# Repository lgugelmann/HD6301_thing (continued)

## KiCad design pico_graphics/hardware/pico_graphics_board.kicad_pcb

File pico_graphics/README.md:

# Pico Graphics

## TODOs for next revision

- reset button for the pico
- figure out the powerup problems
- R/W interface + interrupts

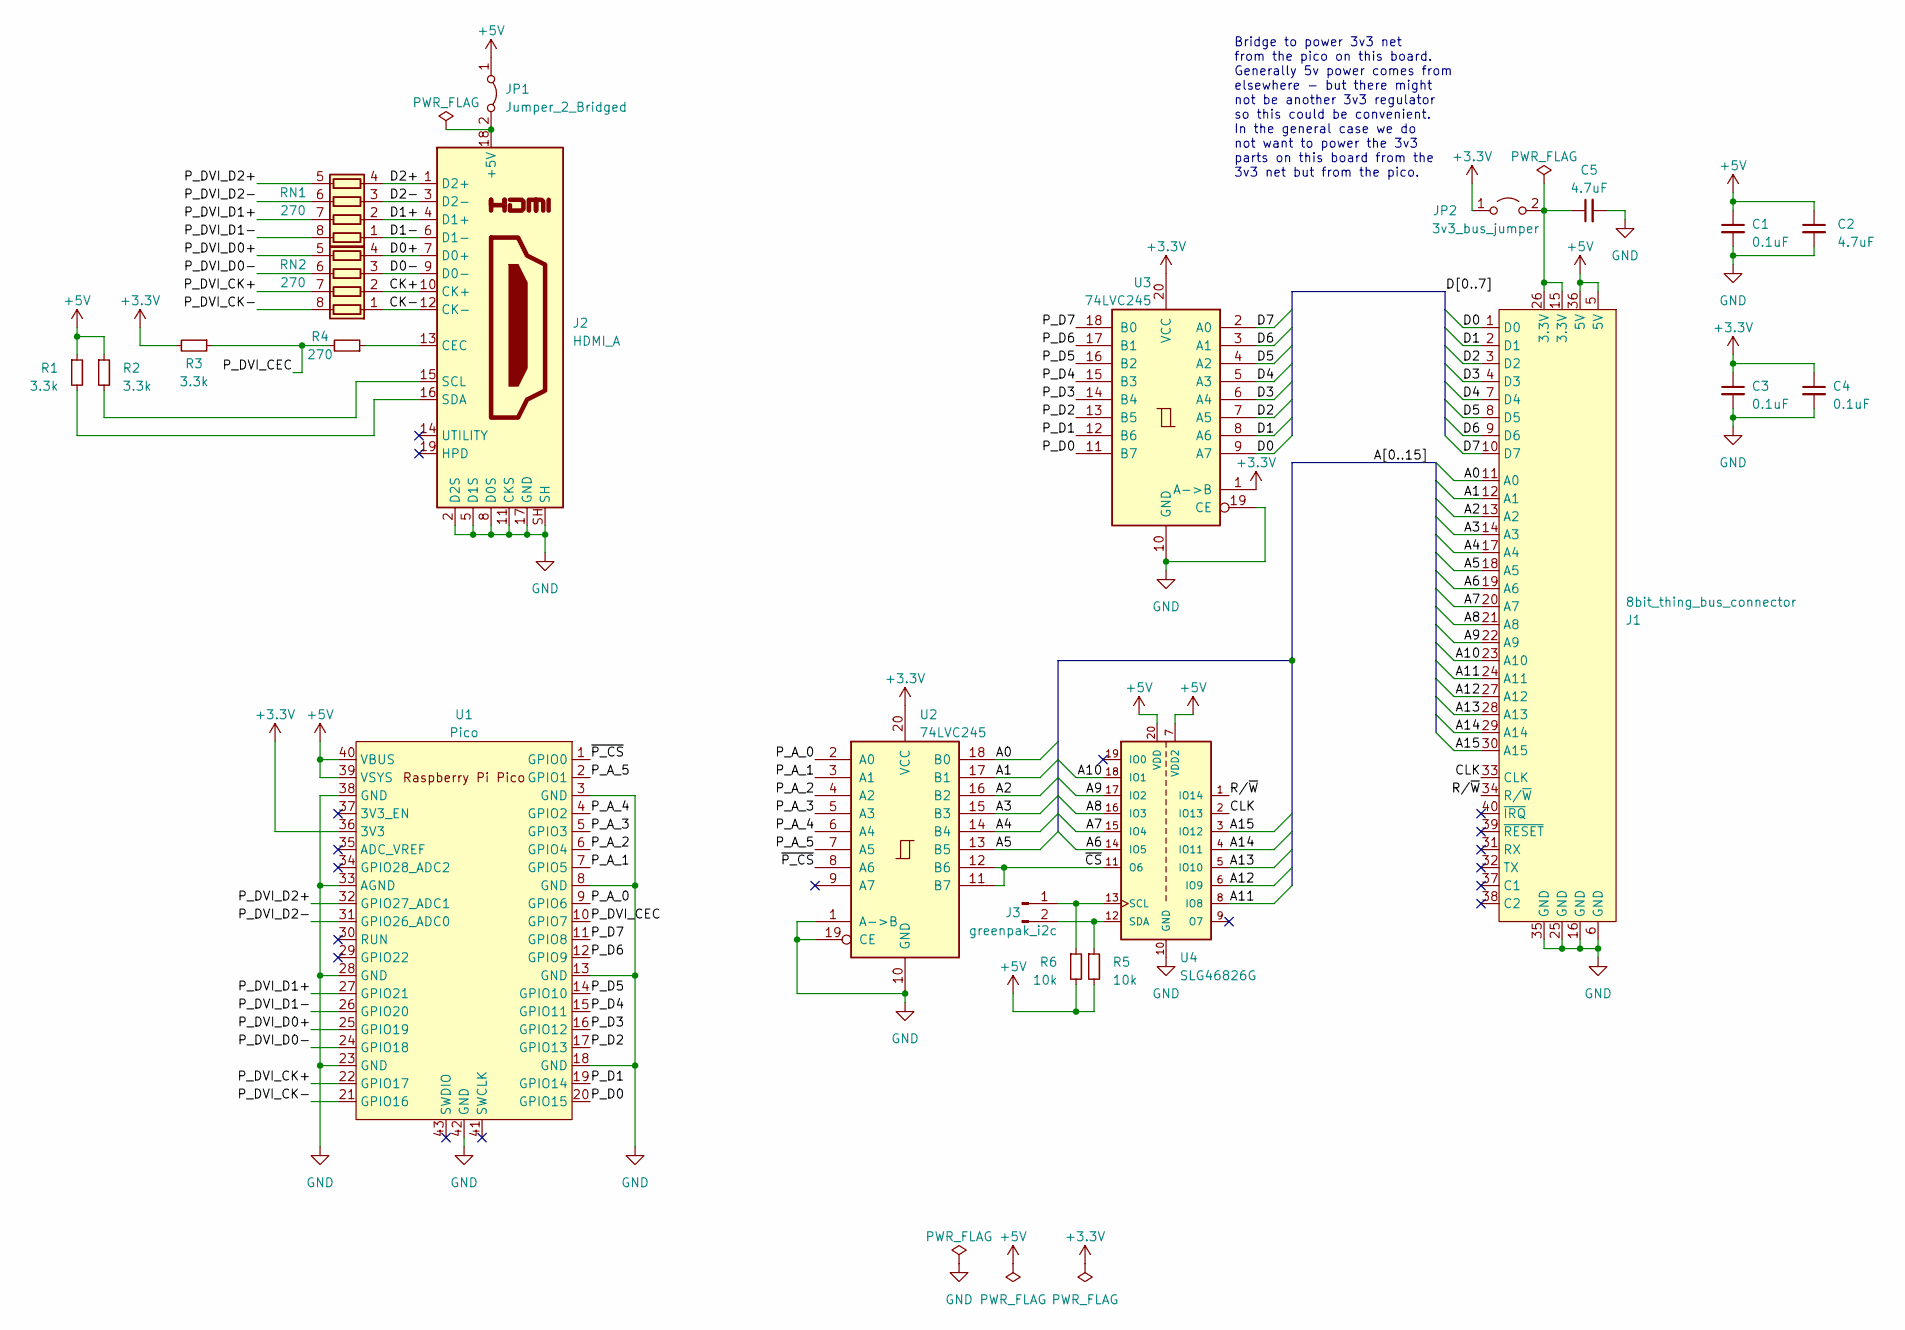
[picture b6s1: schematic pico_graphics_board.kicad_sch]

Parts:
C1, C3, C4: 0.1uF; C_0805_2012Metric_Pad1.18x1.45mm_HandSolder
C2, C5: 4.7uF; C_0805_2012Metric_Pad1.18x1.45mm_HandSolder
J1: 8bit_thing_bus_connector; IDC-Header_2x20_P2.54mm_Horizontal
J2: HDMI_A; HDMI_A_Amphenol_10029449-x01xLF_Horizontal
J3: greenpak_i2c; PinHeader_1x02_P2.54mm_Vertical_minimal
JP1: Jumper_2_Bridged; R_0805_2012Metric_Pad1.20x1.40mm_HandSolder
JP2: 3v3_bus_jumper; PinHeader_1x02_P2.54mm_Vertical_minimal
R1, R2, R3: 3.3k; R_0805_2012Metric_Pad1.20x1.40mm_HandSolder
R4: 270; R_0805_2012Metric_Pad1.20x1.40mm_HandSolder
R5, R6: 10k; R_0805_2012Metric_Pad1.20x1.40mm_HandSolder
RN1, RN2: 270; R_Array_Concave_4x0603
U1: Pico; RPi_Pico_SMD_TH
U2, U3: 74LVC245; TSSOP-20_4.4x6.5mm_P0.65mm
U4: SLG46826G; TSSOP-20_4.4x6.5mm_P0.65mm; PARTREV 3.10

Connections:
+3.3V: C3.1, C4.1, JP2.1 (A), R3.2, U1.36 (3V3), U2.20 (VCC), U3.1 (A->B), U3.20 (VCC)
+5V: C1.1, C2.1, J1.5 (5V), J1.36 (5V), JP1.1 (A), R1.1, R2.1, R5.2, R6.2, U1.39 (VSYS), U1.40 (VBUS), U4.7 (VDD2), U4.20 (VDD)
/A0: J1.11 (A0), U2.18 (B0)
/A1: J1.12 (A1), U2.17 (B1)
/A2: J1.13 (A2), U2.16 (B2)
/A3: J1.14 (A3), U2.15 (B3)
/A4: J1.17 (A4), U2.14 (B4)
/A5: J1.18 (A5), U2.13 (B5)
/A6: J1.19 (A6), U4.14 (IO5)
/A7: J1.20 (A7), U4.15 (IO4)
/A8: J1.21 (A8), U4.16 (IO3)
/A9: J1.22 (A9), U4.17 (IO2)
/A10: J1.23 (A10), U4.18 (IO1)
/A11: J1.24 (A11), U4.8 (IO8)
/A12: J1.27 (A12), U4.6 (IO9)
/A13: J1.28 (A13), U4.5 (IO10)
/A14: J1.29 (A14), U4.4 (IO11)
/A15: J1.30 (A15), U4.3 (IO12)
/CK+: J2.10 (CK+), RN2.2 (R2.1)
/CK-: J2.12 (CK-), RN2.1 (R1.1)
/CLK: J1.33 (CLK), U4.2 (IO13)
/D0: J1.1 (D0), U3.9 (A7)
/D0+: J2.7 (D0+), RN2.4 (R4.1)
/D0-: J2.9 (D0-), RN2.3 (R3.1)
/D1: J1.2 (D1), U3.8 (A6)
/D1+: J2.4 (D1+), RN1.2 (R2.1)
/D1-: J2.6 (D1-), RN1.1 (R1.1)
/D2: J1.3 (D2), U3.7 (A5)
/D2+: J2.1 (D2+), RN1.4 (R4.1)
/D2-: J2.3 (D2-), RN1.3 (R3.1)
/D3: J1.4 (D3), U3.6 (A4)
/D4: J1.7 (D4), U3.5 (A3)
/D5: J1.8 (D5), U3.4 (A2)
/D6: J1.9 (D6), U3.3 (A1)
/D7: J1.10 (D7), U3.2 (A0)
/P_A_0: U1.9 (GPIO6), U2.2 (A0)
/P_A_1: U1.7 (GPIO5), U2.3 (A1)
/P_A_2: U1.6 (GPIO4), U2.4 (A2)
/P_A_3: U1.5 (GPIO3), U2.5 (A3)
/P_A_4: U1.4 (GPIO2), U2.6 (A4)
/P_A_5: U1.2 (GPIO1), U2.7 (A5)
/P_D0: U1.20 (GPIO15), U3.11 (B7)
/P_D1: U1.19 (GPIO14), U3.12 (B6)
/P_D2: U1.17 (GPIO13), U3.13 (B5)
/P_D3: U1.16 (GPIO12), U3.14 (B4)
/P_D4: U1.15 (GPIO11), U3.15 (B3)
/P_D5: U1.14 (GPIO10), U3.16 (B2)
/P_D6: U1.12 (GPIO9), U3.17 (B1)
/P_D7: U1.11 (GPIO8), U3.18 (B0)
/P_DVI_CEC: R3.1, R4.2, U1.10 (GPIO7)
/P_DVI_CK+: RN2.7 (R2.2), U1.22 (GPIO17)
/P_DVI_CK-: RN2.8 (R1.2), U1.21 (GPIO16)
/P_DVI_D0+: RN2.5 (R4.2), U1.25 (GPIO19)
/P_DVI_D0-: RN2.6 (R3.2), U1.24 (GPIO18)
/P_DVI_D1+: RN1.7 (R2.2), U1.27 (GPIO21)
/P_DVI_D1-: RN1.8 (R1.2), U1.26 (GPIO20)
/P_DVI_D2+: RN1.5 (R4.2), U1.32 (GPIO27_ADC1)
/P_DVI_D2-: RN1.6 (R3.2), U1.31 (GPIO26_ADC0)
/R/~W: J1.34 (R/~W), U4.1 (IO14)
/~CS: U2.11 (B7), U2.12 (B6), U4.11 (O6)
/~P_CS: U1.1 (GPIO0), U2.8 (A6)
GND: C1.2, C2.2, C3.2, C4.2, C5.2, J1.6 (GND), J1.16 (GND), J1.25 (GND), J1.35 (GND), J2.2 (D2S), J2.5 (D1S), J2.8 (D0S), J2.11 (CKS), J2.17 (GND), J2.SH, U1.3 (GND), U1.8 (GND), U1.13 (GND), U1.18 (GND), U1.23 (GND), U1.28 (GND), U1.33 (AGND), U1.38 (GND), U1.42 (GND), U2.1 (A->B), U2.10 (GND), U2.19 (CE), U3.10 (GND), U3.19 (CE), U4.10 (GND)
unnamed: J2.18 (+5V), JP1.2 (B)
unnamed: J2.13 (CEC), R4.1
unnamed: J2.15 (SCL), R2.2
unnamed: J2.16 (SDA), R1.2
unnamed: J3.1, R6.1, U4.13 (SCL)
unnamed: J3.2, R5.1, U4.12 (SDA)
unnamed: C5.1, J1.15 (3.3V), J1.26 (3.3V), JP2.2 (B)

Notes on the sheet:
Bridge to power 3v3 net from the pico on this board. Generally 5v power comes from elsewhere - but there might not be another 3v3 regulator so this could be convenient. In the general case we do not want to power the 3v3 parts on this board from the 3v3 net but from the pico.

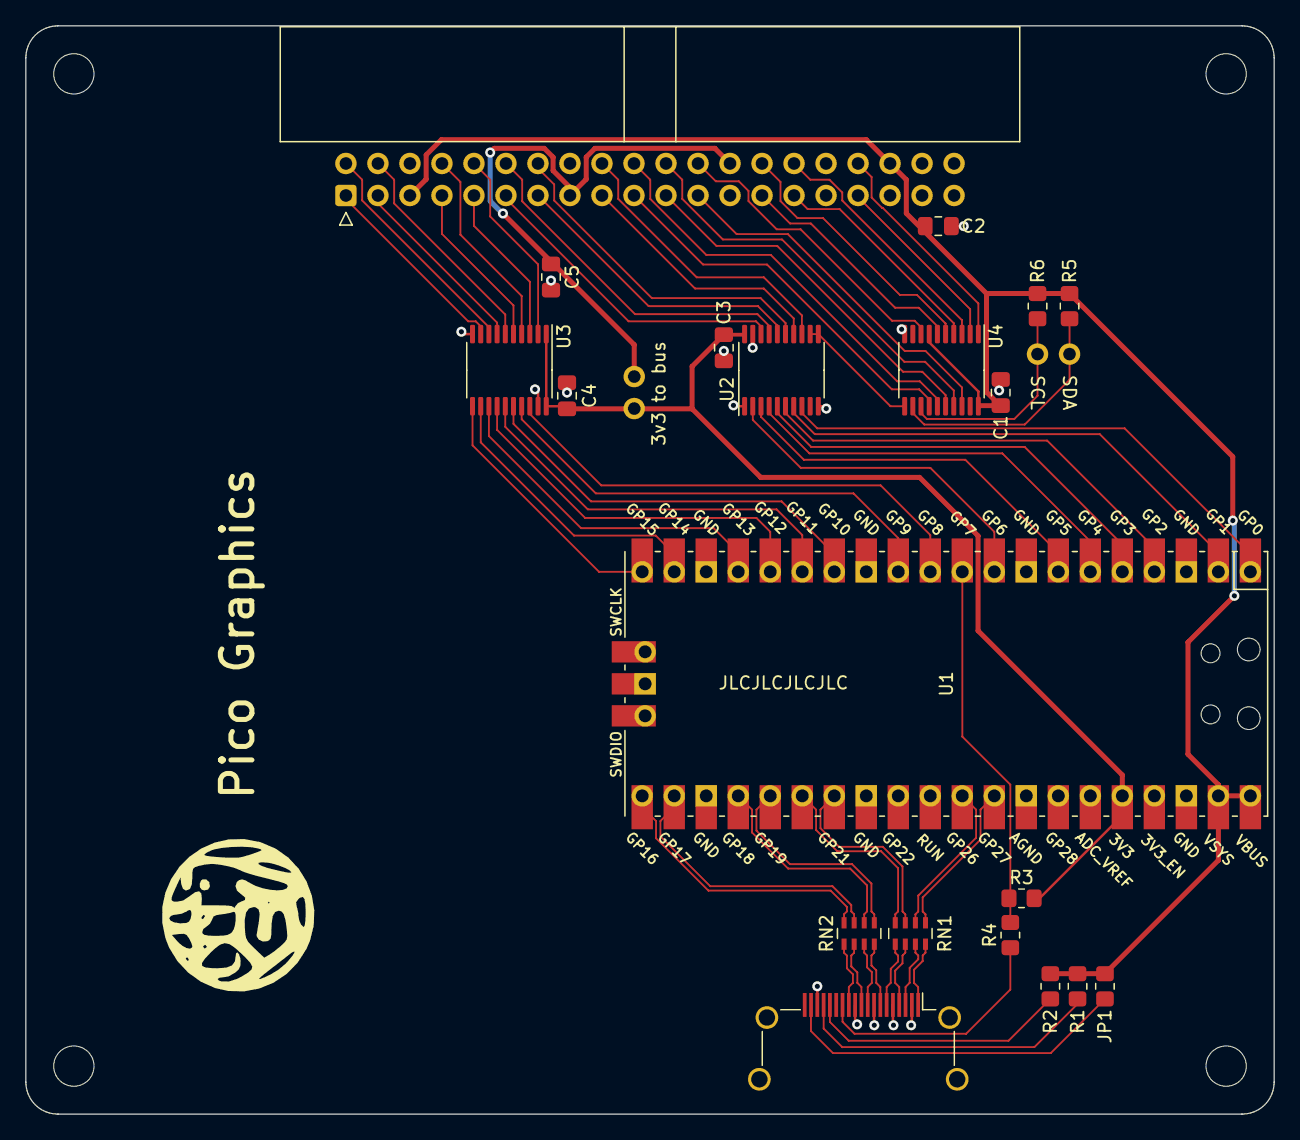
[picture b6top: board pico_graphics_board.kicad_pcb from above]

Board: 2 copper layers, 99.1 x 86.4 mm, 22 parts (0 on the bottom side), 69 nets.

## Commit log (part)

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2023-12-28 MIDI board v1 schematic & PCB
2023-12-29 Final v1 version of the MIDI/UART board
    - Tightened the layout a bit
    - Added jumpers to select whether the second MIDI port is OUT or THRU
    - Moved jumpers for system RX/TX connection to a better place
    - Added labels for everything on the silkscreen
2024-01-03 MIDI board: remove outdated comment from schematic
2024-01-04 MIDI synth, workable version
    This plays some MIDI somewhat reasonably - lots of missing features still, like
    proper volume handling.
2024-02-04 MIDI Synth: support polyphony
    Before this change we allocated each MIDI channel to a fixed OPL3 channel, which
    allowed only one note to be played per channel. This changes the playing logic
    to dynamically allocate OPL channels to incoming MIDI notes, with some attempts
    to reuse already-set-up channels to avoid constantly reloading instruments. We
    can now play an arbitrary number of simultaneous notes across all MIDI channels,
    as long as the total number is less than 18 (the max number of OPL3 channels).
2024-02-05 MIDI synth: add MIDI channel 10 support
2024-02-10 TMB/ASM converter: output a comment with the patch number
2024-02-10 Add a comment with instrument number to the GM instruments bank
2024-03-17 Initial 6301 emulator code
    This runs the monitor until keyboard input is requested so it's somewhat functional. It's not pretty though...
2024-03-21 Emulator: add basic SDL2 keyboard, window support
2024-03-29 Fix emulator cpu tick() to actually fetch new opcodes
2024-03-31 Add .gitignore file to ignore build directory
2024-03-31 Emulator: Add interrupt handling functionality
2024-03-31 Emulator: add PS2 keyboard support
2024-03-31 Graphics emulation: actually clear graphics on clear command
2024-03-31 Graphics: proper locking while changing rendering surface
2024-04-01 Refactor get16 and set16 methods in AddressSpace class
2024-04-01 Emulator: stop timer before shutdown
    The separate timer thread causes deinitialization order issues on shutdown.
2024-04-02 Update PicoDVI subproject commit hash
2024-04-02 opl3_test.s: add test using sound_stop_midi_note
2024-04-02 Fix incorrect parameter order in ABA instruction
2024-04-02 Fix STX opcode mnemonic in Cpu6301
2024-04-03 Emulator: add README.md
2024-04-07 Emulator: add OPL3 sound board emulation class
2024-04-12 Add HD6301Serial class emulating the HD6301 SCI
2024-04-12 Emulator: small init error handling change
2024-04-13 Refactor Rom class to use factory function and absl::StatusOr for error handling
2024-04-13 Emulator: use QCHECK / LOG(FATAL) everywhere for consistency in emulator.cc
2024-04-13 Emulator: add MidiToSerial class for forwarding MIDI bytes to a PTY
2024-04-14 Emulator: update and extend documentation
2024-04-14 Update emulator documentation with details on profiling with gperftools
2024-04-14 Emulator: fixes to make the code compile with clang++ and strict warnings as errors
    Turns out clang is a bit more aggressive about undefined variables. There is also some weirdness about undefined references to operator<< on LOG()s with uint8/16_t that needs to be worked around.
2024-04-17 Emulator: make Ps2Keyboard thread safe
2024-04-17 Update emulator build instructions and profiling/sanitizer documentation
2024-04-20 Emulator: remove graphics_tester
2024-04-20 Emulator: add Dear ImGui dependency
2024-04-20 Emulator: don't steal keyboard focus away from the emulator
2024-04-24 Update .vscode settings for multi-project setup
2024-04-26 ASM: Add a simple test program for IO board functionality
2024-05-01 Emulator: add class for basic WD65C22 emulation
    This only supports port A/B IO and data direction registers.
2024-05-01 ASM: add 10ms delay function
2024-05-02 Emulator: correctly return 'illegal' for unknown SD commands
2024-05-03 Emulator: add flags to load SD card image files
2024-05-05 ASM: create constants for memory map, move system memory boundaries
    The constants make it easier to move the boundaries betwee user and system
    memory. This also moves 512 bytes more into the system memory area in
    preparation of moving sd card buffers there.
2024-05-09 Add 'googletest' as a new submodule
    With the growing number of dependencies and sub-projects this one is going into
    a 'dependencies' folder. Eventually we should move every dependency there too to
    keep things neat.
2024-05-09 Emulator: add unit tests for hexdump
2024-05-09 Move PicoDVI to the dependencies folder too
2024-05-09 Add a script to generate font.h and regenerate the header itself
2024-05-12 Emulator: disable imgui.ini files
2024-05-12 Disassembler: rework the vector decoding a bit
    - Don't return an error when no decoding happens. Not every piece of code has them.
    - Be more careful about clobbering existing annotations (should be a no-op though)
    - Annotate the 2nd byte of the address to be skipped
2024-05-12 Emulator: turn off ClangTidy builds by default
2024-05-18 ASM: rename 'ls' to 'list'
2024-05-20 ASM: remove io_test program, that functionality is now in the 'file' module
2024-05-28 Monitor: implement 'cat'
2024-06-02 ASM: add file_at_eof function
2024-06-07 ASM: use inc16 to replace some code in file.inc
2024-06-15 file.inc: add support to read files up to 1 cluster in size
2024-06-23 Extract the graphics state code into its own library
    Currently there are two implementations, one in pico_graphics and one in the
    emulator. This allows consolidating down to one.
2024-07-06 Graphics state: implement video roll functionality
    This makes it cheap to define where the top line should be without having to
    copy entire buffers around. It does require an implementation on the video
    driver side however.
2024-07-07 Monitor: put command line parameter pointer in the user stack
    This makes it possible to pass parameters to user programs.
2024-09-09 MIDI decoder: initial code to decode a MIDI file, missing most functionality
    This goes as far as parsing headers and some basic messages. It lacks
    functionality to read beyond one sector too.
2024-09-09 Fix a bug in 'file.inc' which caused premature ends to reads in some cases
2024-11-08 ASM: Fix read of the last sector for files of size k*512 bytes
    If the last sector was exactly 512 bytes the current code returned a size 0 read
    instead of 512.
2024-11-09 Emulator: remove an extra stray semicolon
2024-11-09 Emulator: increase preformance by avoiding some expensive locking
    A good 25% of emulator time is spent just locking locks on each tick to find out
    whether we have interrupts or whether there is serial data waiting. These
    conditions are almost always false and we can drastically improve performance by
    replacing them with an atomic flag that is much cheaper to test in the false
    case.
2024-11-09 Emulator: update instruction setup code to populate the array directly
2024-11-15 Update w65c22 demo program to include IRQ example
2024-11-16 Optimize SPI byte reading code for 25% faster sd card reads
2024-11-23 Document and simplify some of the locking in the emulator
2024-12-20 Update schematic for IO board
2024-12-21 W65C22 emulation: improve timer alignment between emulation and real hardware
    The real hardware keeps the counters at N for a cycle, the emulation decremented
    them by one already at that time.
2024-12-22 ASM: Updated SPI module to use the 65c22 SR/parallel port approach
    This is a working version, but it has a large number of delays built in. It does
    512 bytes in 34ms. We can do better!
2024-12-27 Fix 65C22 tests after timer precision changes
2024-12-30 ASM: Allow specifying an autostart program via CMake variables
2024-12-31 Add a git-ignored directory for random stuff
    Sometimes things just aren't useful to be committed, but need to stick around
    anyway. This is for that and to avoid piling up uncommitted files.
2024-12-31 Remove outdated ft231x programmer code
2025-01-02 Add CMake target to build a default SD image file
2025-01-02 Fix W65C22 emulation: the shift register is MSB- not LSB-first
    This also adds separate constants for pin numbers vs port masks to avoid
    confusion.
2025-01-04 ASM: Add spi_receive_block in spi.inc to read 512 bytes at a time
    This should be nearly optimal as it's 18 cycles per byte (plus setup), which is
    as fast as the shift register can go.
2025-01-19 IO board: update the schematic to use '595 for SD Card --> 65C22 comms
2025-01-21 ASM: initialize i2c in the monitor
2025-01-26 Emulator: Implement SPI using provide_input() instead of read callbacks
2025-01-26 IOPort: remove unused read callback code
    This is now all moved to provide_data() and removing the unused callback code
    saves a few cycles.
2025-02-15 Update all Kicad files to the Kicad8 format
    This was done by opening each file and saving it without any changes.
2025-03-08 Rename ps_keyboard.{cc,h} and the code in there to mark it as the 6301 version
    We're going to add a second keyboard interface using the 65C22. This is prep
    work for that.
2025-04-12 Ensure the data present bit is always cleared in 6301 keyboard emulation
    In the current code this can get stuck on. It used to be cleared because the
    6301 keyboard always got data when the IRQ code fired. That's not longer the
    case.
2025-04-23 Update Nuked/Abseil/GoogleTest dependencies to the latest version
2025-04-26 Mostly routed IO board
    It's still missing:
    - An i2c timer
    - All the sanity checks
    - Making all GreenPAK code match the schematic. Many pins were moved for easier
    routing.
    - Aligning the PS2 port with other ports on other boards.
2025-07-02 Add unit tests for LSRD and ASLD instructions
    Adds comprehensive unit tests for the LSRD (Logical Shift Right Double)
    and ASLD (Arithmetic Shift Left Double) instructions in the Cpu6301
    emulator.
    The tests cover the following scenarios:
    - Basic shift operations
    - Shifts resulting in a zero value and setting the Zero flag
2025-07-02 Add unit tests for CLV and SEV instructions
    Adds unit tests for the CLV (Clear Overflow) and SEV (Set Overflow)
    instructions.
    AI generated
2025-07-02 Add unit tests for CBA instruction
    Adds unit tests for the CBA (Compare Accumulators) instruction.
    The tests cover:
    - A standard comparison.
    - A comparison resulting in zero, ensuring the Zero flag is set.
    - A comparison resulting in a negative number, ensuring the Negative and Carry flags are set.
    AI generated
2025-07-06 Add unit tests for PSHA and PSHB instructions
    Adds unit tests for:
    - PSHA (Push Accumulator A to Stack)
    - PSHB (Push Accumulator B to Stack)
    AI generated
2025-07-07 Fix BITB instruction and add tests
    Corrects the BITB instruction implementation to use accumulator B instead of A. Adds unit tests for the AND and BIT instructions to verify their functionality and cover different addressing modes.
    AI-generated
2025-07-26 Add the next set of AI-generated instruction tests
2026-03-22 Add declarative instruction test infrastructure
    Introduce a new test framework for CPU instruction tests using a simple
    declarative text format (.test files). Each file contains test cases
    separated by '---' with fields for: initial state (setup), instruction
    bytes (memory), pre-loaded memory (at XXXX), expected post-execution
    state (expect), expected memory (expect_at XXXX), and cycle count.
    New files:
2026-03-22 Add comprehensive instruction test coverage (314 tests)
    Add 67 new .test files covering all previously untested instructions:
    - All 16 branch instructions (BRA, BRN, BHI, BLS, BCC, BCS, BNE, BEQ,
    BVC, BVS, BPL, BMI, BGE, BLT, BGT, BLE)
    - Accumulator A ops: COMA, LSRA, RORA, ASRA, ASLA, ROLA, DECA, INCA,
    TSTA, CLRA
    - Accumulator B ops: COMB, LSRB, RORB, ASRB, ASLB, ROLB, DECB, INCB,
2026-03-22 Add Google Benchmark as a git submodule
